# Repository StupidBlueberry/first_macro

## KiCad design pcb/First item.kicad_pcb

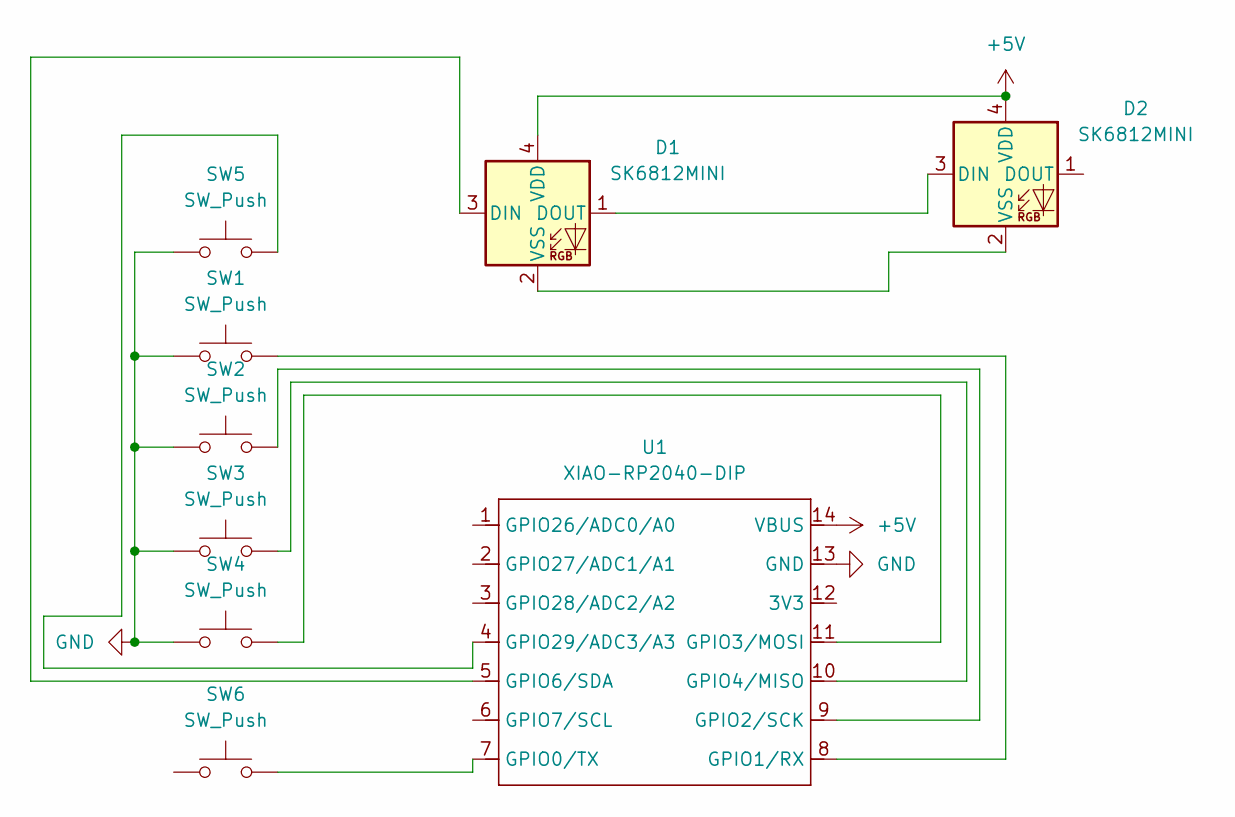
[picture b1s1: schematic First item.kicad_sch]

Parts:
D1, D2: SK6812MINI; LED_SK6812MINI_PLCC4_3.5x3.5mm_P1.75mm
SW1, SW2, SW3, SW4, SW5, SW6: SW_Push; SW_Cherry_MX_1.00u_PCB
U1: XIAO-RP2040-DIP

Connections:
+5V: D1.4 (VDD), D2.4 (VDD), U1.14 (VBUS)
GND: SW1.1, SW2.1, SW3.1, SW4.1, SW5.1, U1.13 (GND)
unnamed: D1.3 (DIN), U1.5 (GPIO6/SDA)
unnamed: D1.1 (DOUT), D2.3 (DIN)
unnamed: D1.2 (VSS), D2.2 (VSS)
unnamed: SW6.2, U1.7 (GPIO0/TX)
unnamed: SW1.2, U1.8 (GPIO1/RX)
unnamed: SW2.2, U1.9 (GPIO2/SCK)
unnamed: SW4.2, U1.11 (GPIO3/MOSI)
unnamed: SW3.2, U1.10 (GPIO4/MISO)
unnamed: SW5.2, U1.4 (GPIO29/ADC3/A3)

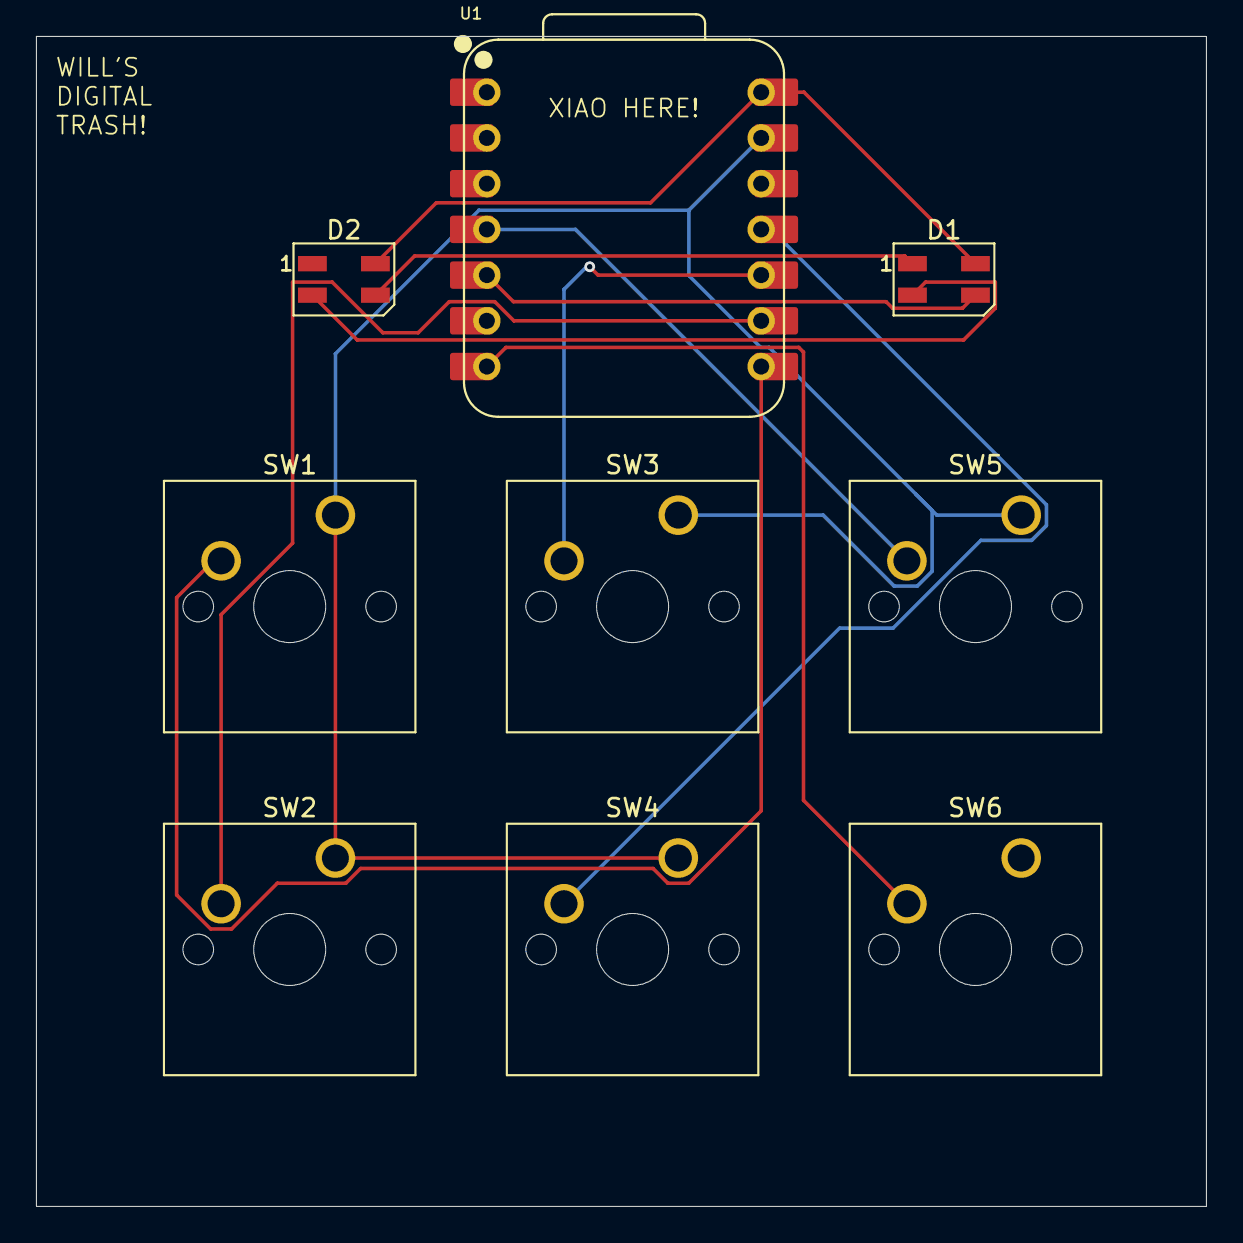
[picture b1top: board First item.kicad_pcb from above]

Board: 2 copper layers, 65.0 x 65.0 mm, 9 parts (0 on the bottom side), 11 nets.

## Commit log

2025-06-16 pcb and firmware v1
2025-06-16 gitignore
2025-06-16 rm ds store
